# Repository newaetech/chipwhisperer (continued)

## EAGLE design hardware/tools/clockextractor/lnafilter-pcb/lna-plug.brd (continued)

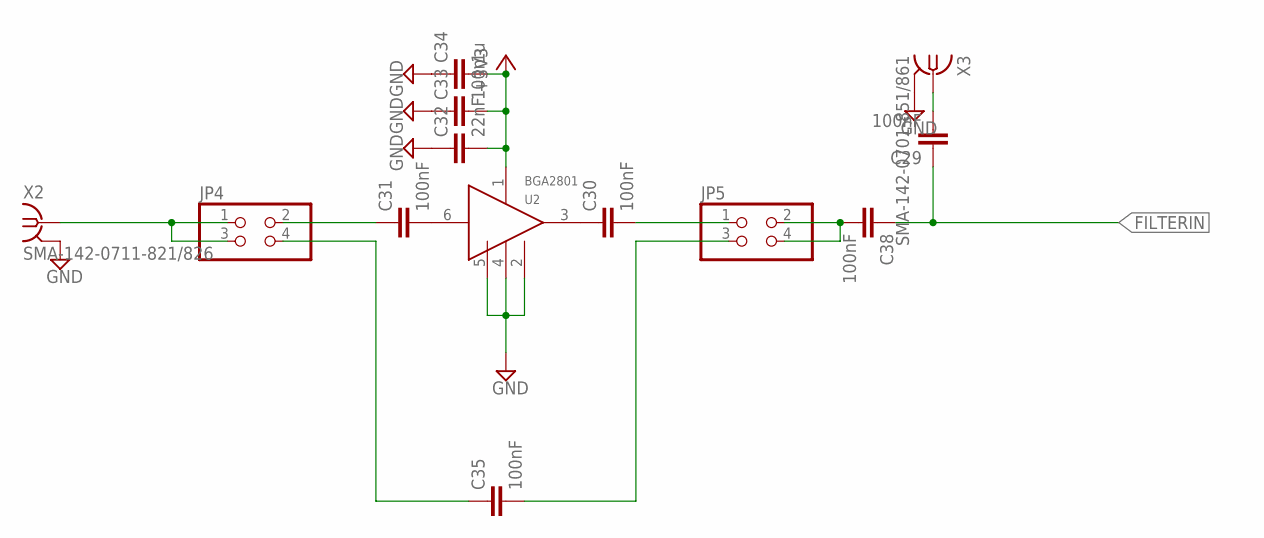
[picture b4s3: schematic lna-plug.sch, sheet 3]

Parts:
C29, C30, C31, C35, C38: 100nF; C0603
C32: 22nF; C0603
C33: 100n; C0603
C34: 1u; C0603
JP4, JP5: PINHD-2X2; 2X02
U2: BGA2801; SOTT323-6
X2: SMA-142-0711-821/826; J502-ND-142-0711-821/826
X3: SMA-142-0701-851/861; J502-ND-142-0701-851/861

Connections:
+3V3: C32.2, C33.2, C34.2, U2.1 (VCC); also elsewhere on the board
FILTERIN: C29.1, C38.1; also elsewhere on the board
GND: C32.1, C33.1, C34.1, U2.2 (GND), U2.4 (GND), U2.5 (GND), X2.G@1 (2), X2.G@2 (2), X2.G@3 (2), X2.G@4 (2), X3.G@1 (2), X3.G@2 (2), X3.G@3 (2), X3.G@4 (2); also elsewhere on the board
unnamed: C38.2, JP5.2, JP5.4
unnamed: C29.2, X3.1
unnamed: C30.1, U2.3 (OUT)
unnamed: C31.2, U2.6 (IN)
unnamed: JP4.1, JP4.3, X2.1
unnamed: C31.1, JP4.2
unnamed: C30.2, JP5.1
unnamed: C35.1, JP4.4
unnamed: C35.2, JP5.3

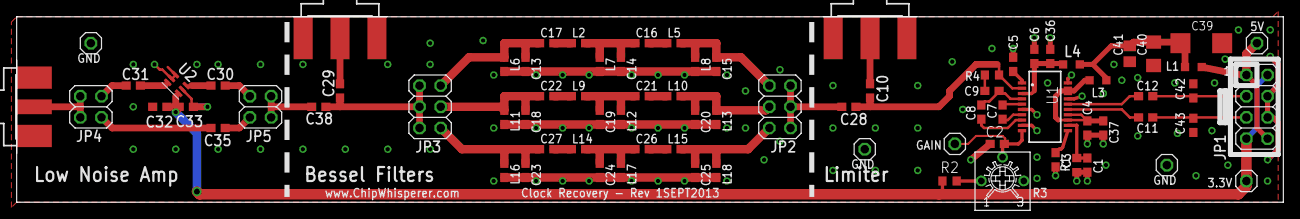
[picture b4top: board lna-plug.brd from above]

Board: 2 copper layers, 151.7 x 22.2 mm, 81 parts (1 on the bottom side), 48 nets.

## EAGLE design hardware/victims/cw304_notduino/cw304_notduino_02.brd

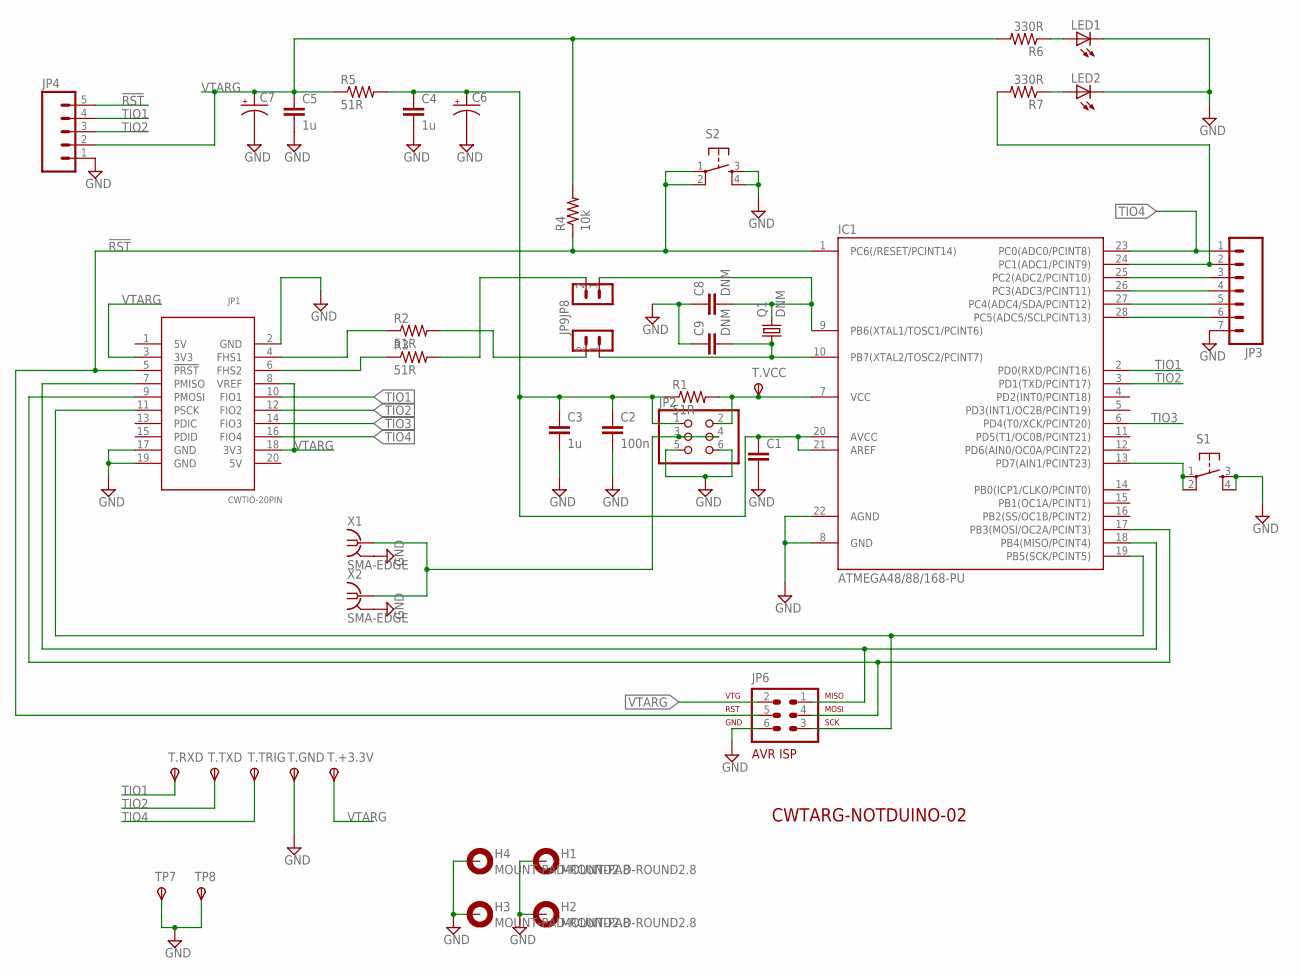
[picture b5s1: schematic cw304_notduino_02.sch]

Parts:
C1: CAPPTH; CAP-PTH-SMALL
C2: 100n; CAP-PTH-SMALL
C3, C4, C5: 1u; CAP-PTH-SMALL
C6, C7: CAP_POLPTH1; CPOL-RADIAL-100UF-25V
C8, C9: DNM; CAP-PTH-SMALL
H1, H2, H3, H4: MOUNT-PAD-ROUND2.8; 2,8-PAD
IC1: ATMEGA48/88/168-PU; DIL28-3
JP1: CWTIO-20PIN; PINSHRD_PTH_2X10
JP2: PINHD-2X3; 2X03
JP3: M07LOCK; 1X07_LOCK
JP4: M05LOCK; 1X05_LOCK
JP6: AVR-ISP-6
JP8, JP9: M02LOCK; 1X02_LOCK
LED1, LED2: LED5MM
Q1: DNM; HC49U-V
R1, R2, R3, R5: 51R; AXIAL-0.4
R4: 10k; AXIAL-0.4
R6, R7: 330R; AXIAL-0.4
S1, S2: TAC_SWITCHPTH; TACTILE-PTH
T.+3.3V, T.GND, T.RXD, T.TRIG, T.TXD: TPSPAD1-13; P1-13
T.VCC: TPSPAD1-17; P1-17
TP7, TP8: TPSPAD1-17; P1-17
X1, X2: SMA-EDGE; J502-ND-142-0711-821/826

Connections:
!RST: IC1.1 (PC6(/RESET/PCINT14)), JP1.5 (!PRST), JP4.5, JP6.5, R4.P$1 (1), S2.1, S2.2
GND: C1.2, C2.2, C3.2, C4.2, C5.2, C6.2 (-), C7.2 (-), C8.1, C9.1, H1.B2,8, H2.B2,8, H3.B2,8, H4.B2,8, IC1.8 (GND), IC1.22 (AGND), JP1.2 (GND), JP1.17 (GND), JP1.19 (GND), JP2.5, JP2.6, JP3.7, JP4.1, JP6.6, LED1.K (C), LED2.K (C), S1.3, S1.4, S2.3, S2.4, T.GND.TP, TP7.TP, TP8.TP, X1.G@1 (2), X1.G@2 (2), X1.G@3 (2), X1.G@4 (2), X2.G@1 (2), X2.G@2 (2), X2.G@3 (2), X2.G@4 (2)
unnamed: LED2.A, R7.P$1 (1)
unnamed: IC1.18 (PB4(MISO/PCINT4)), JP1.7 (PMISO), JP6.1
unnamed: IC1.17 (PB3(MOSI/OC2A/PCINT3)), JP1.9 (PMOSI), JP6.4
unnamed: JP1.4 (FHS1), R2.P$1 (1)
unnamed: JP1.6 (FHS2), R3.P$1 (1)
unnamed: IC1.19 (PB5(SCK/PCINT5)), JP1.11 (PSCK), JP6.3
unnamed: IC1.7 (VCC), JP2.2, R1.P$2 (2), T.VCC.TP
unnamed: LED1.A, R6.P$1 (1)
unnamed: C1.1, C2.1, C3.1, C4.1, C6.1 (+), IC1.20 (AVCC), IC1.21 (AREF), JP2.1, R1.P$1 (1), R5.P$2 (2)
unnamed: C8.2, IC1.9 (PB6(XTAL1/TOSC1/PCINT6)), JP8.1, Q1.2
unnamed: IC1.13 (PD7(AIN1/PCINT23)), S1.1, S1.2
unnamed: IC1.24 (PC1(ADC1/PCINT9)), JP3.2, R7.P$2 (2)
unnamed: IC1.25 (PC2(ADC2/PCINT10)), JP3.3
unnamed: IC1.26 (PC3(ADC3/PCINT11)), JP3.4
unnamed: IC1.27 (PC4(ADC4/SDA/PCINT12)), JP3.5
unnamed: IC1.28 (PC5(ADC5/SCLPCINT13)), JP3.6
unnamed: JP2.3, JP2.4, X1.1, X2.1
unnamed: C9.2, IC1.10 (PB7(XTAL2/TOSC2/PCINT7)), JP9.1, Q1.1
THS1: JP9.2, R2.P$2 (2)
THS2: JP8.2, R3.P$2 (2)
TIO1: IC1.2 (PD0(RXD/PCINT16)), JP1.10 (FIO1), JP4.4, T.RXD.TP
TIO2: IC1.3 (PD1(TXD/PCINT17)), JP1.12 (FIO2), JP4.3, T.TXD.TP
TIO3: IC1.6 (PD4(T0/XCK/PCINT20)), JP1.14 (FIO3)
TIO4: IC1.23 (PC0(ADC0/PCINT8)), JP1.16 (FIO4), JP3.1, T.TRIG.TP
VTARG: C5.1, C7.1 (+), JP1.3 (3V3), JP1.8 (VREF), JP1.18 (3V3), JP4.2, JP6.2, R4.P$2 (2), R5.P$1 (1), R6.P$2 (2), T.+3.3V.TP

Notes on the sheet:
CWTARG-NOTDUINO-02

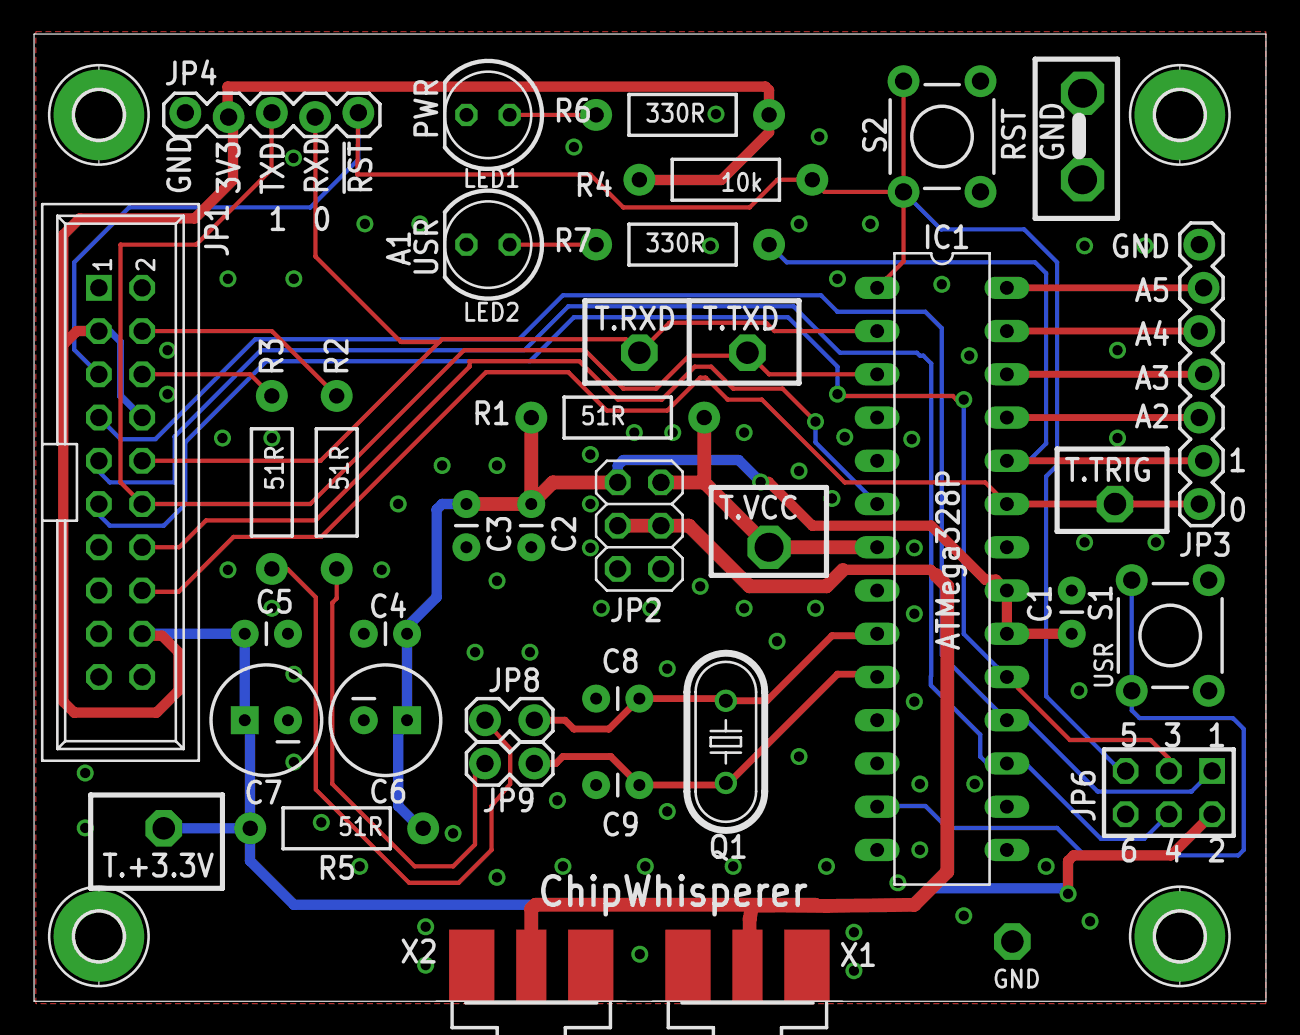
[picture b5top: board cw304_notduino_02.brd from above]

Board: 2 copper layers, 72.4 x 56.8 mm, 43 parts (0 on the bottom side), 27 nets.

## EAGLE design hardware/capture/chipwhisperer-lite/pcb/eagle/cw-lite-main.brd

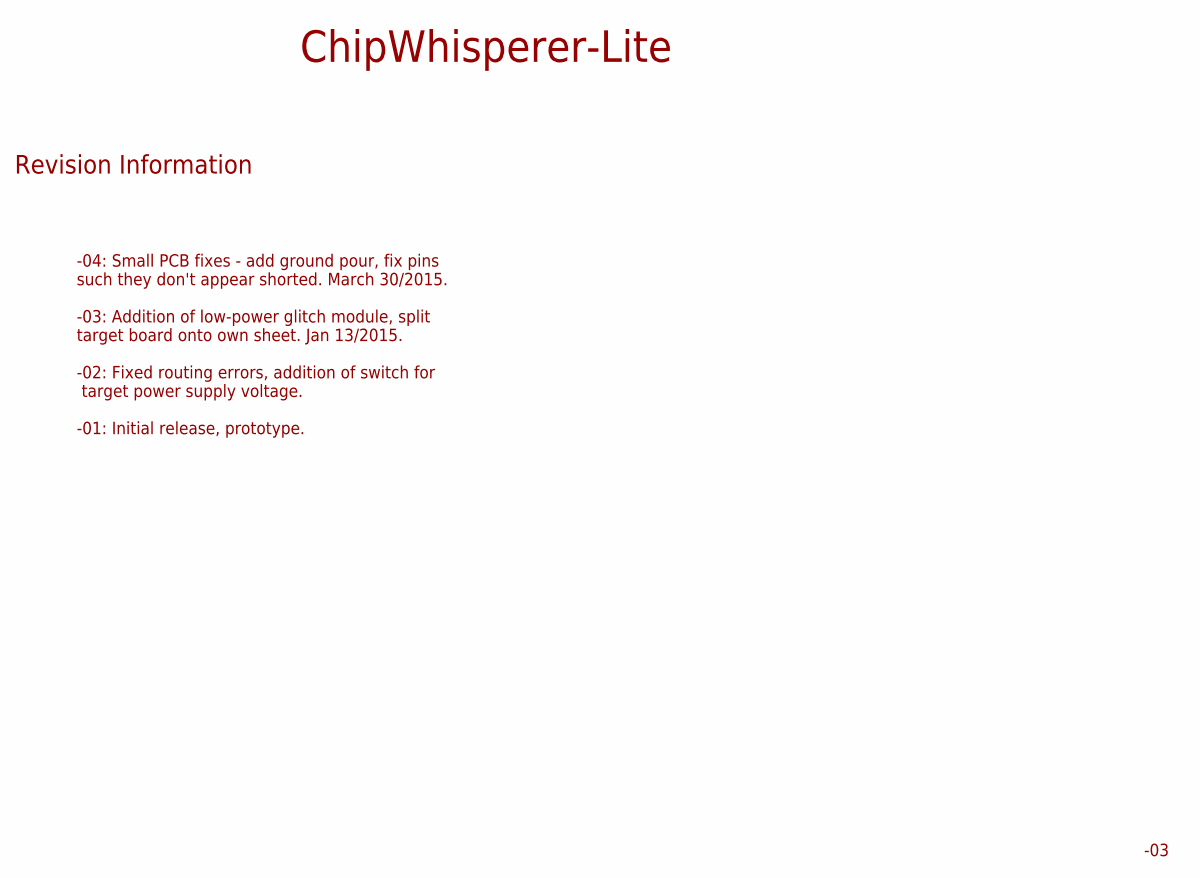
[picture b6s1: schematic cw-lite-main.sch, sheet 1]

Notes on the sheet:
-04: Small PCB fixes - add ground pour, fix pins such they don't appear shorted. March 30/2015. -03: Addition of low-power glitch module, split target board onto own sheet. Jan 13/2015. -02: Fixed routing errors, addition of switch for target power supply voltage. -01: Initial release, prototype.
ChipWhisperer-Lite
Revision Information

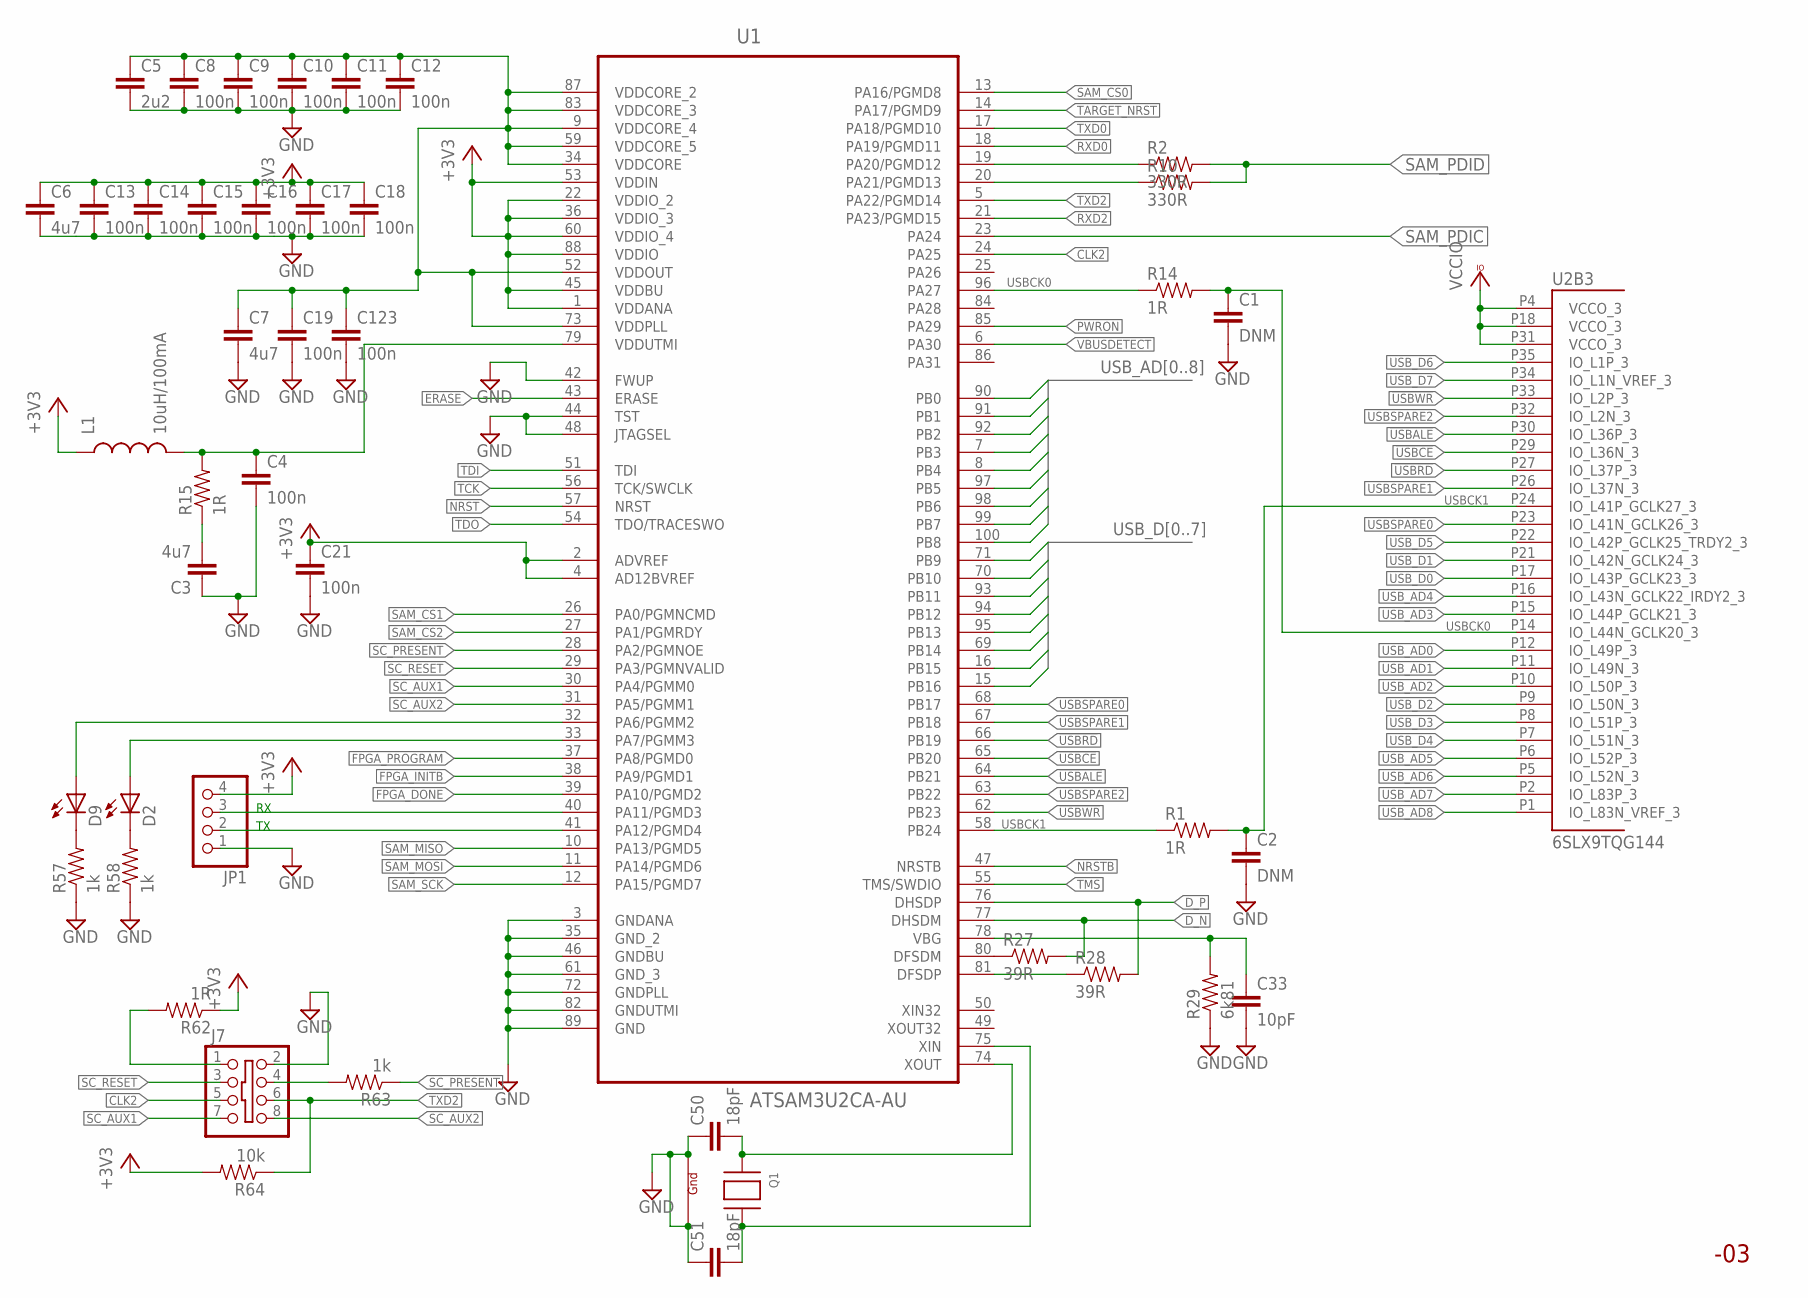
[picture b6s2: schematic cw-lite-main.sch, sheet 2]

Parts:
C1, C2: DNM; 0402C
C3, C6, C7: 4u7; 0603C
C4, C8, C9, C10, C11, C12, C13, C14, C15, C16, C17, C18, C19, C21, C123: 100n; 0402C
C5: 2u2; 0603C
C33: 10pF; 0603C
C50, C51: 18pF; 0402C
D2, D9: LED0603; LED-0603
J7: SHROUD_2X4EDGE; PINSHRD_EDGE_2X04.PAC
JP1: PINHD-1X4; 1X04
L1: 10uH/100mA; 0603
Q1: XTAL-4ABM8G; NX3225; MPN ABM8G-12.000MHZ-4Y-T3
R1, R14: 1R; 0402R
R2, R10: 330R; 0402R
R15, R62: 1R; 0603R
R27, R28: 39R; 0603R
R29: 6k81; 0402R
R57, R58, R63: 1k; 0603R
R64: 10k; 0603R
U1: ATSAM3U2CA-AU; QFP50P1600X1600X160-100N
U2: 6SLX9TQG144; TQ144; MPN XC6SLX9-3TQG144C

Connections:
!USBALE: U1.64 (PB21), U2.P30 (IO_L36P_3)
!USBCE: U1.65 (PB20), U2.P29 (IO_L36N_3)
!USBRD: U1.66 (PB19), U2.P27 (IO_L37P_3)
!USBWR: U1.62 (PB23), U2.P33 (IO_L2P_3)
+3V3: C6.1, C13.1, C14.1, C15.1, C16.1, C17.1, C18.1, C21.1, JP1.4, L1.1, R62.1, R64.2, U1.1 (VDDANA), U1.2 (ADVREF), U1.4 (AD12BVREF), U1.22 (VDDIO_2), U1.36 (VDDIO_3), U1.45 (VDDBU), U1.53 (VDDIN), U1.60 (VDDIO_4), U1.88 (VDDIO); also elsewhere on the board
CLK2: J7.5, U1.24 (PA25); also elsewhere on the board
D_N: R27.2, U1.77 (DHSDM); also elsewhere on the board
D_P: R28.2, U1.76 (DHSDP); also elsewhere on the board
ERASE: U1.43 (ERASE); also elsewhere on the board
FPGA_DONE: U1.39 (PA10/PGMD2); also elsewhere on the board
FPGA_INITB: U1.38 (PA9/PGMD1); also elsewhere on the board
FPGA_PROGRAM: U1.37 (PA8/PGMD0); also elsewhere on the board
GND: C1.2, C2.2, C3.1, C4.2, C5.2, C6.2, C7.2, C8.2, C9.2, C10.2, C11.2, C12.2, C13.2, C14.2, C15.2, C16.2, C17.2, C18.2, C19.2, C21.2, C33.2, C50.1, C51.1, C123.2, J7.2, JP1.1, Q1.2 (G1), Q1.4 (G2), R29.1, R57.1, R58.1, U1.3 (GNDANA), U1.35 (GND_2), U1.42 (FWUP), U1.44 (TST), U1.46 (GNDBU), U1.48 (JTAGSEL), U1.61 (GND_3), U1.72 (GNDPLL), U1.82 (GNDUTMI), U1.89 (GND); also elsewhere on the board
unnamed: R14.1, U1.96 (PA27)
unnamed: JP1.3, U1.40 (PA11/PGMD3)
unnamed: R1.1, U1.58 (PB24)
unnamed: JP1.2, U1.41 (PA12/PGMD4)
unnamed: R2.1, U1.19 (PA20/PGMD12)
unnamed: R10.1, U1.20 (PA21/PGMD13)
unnamed: C3.2, R15.1
unnamed: C4.1, L1.2, R15.2, U1.79 (VDDUTMI)
unnamed: R27.1, U1.80 (DFSDM)
unnamed: C5.1, C7.1, C8.1, C9.1, C10.1, C11.1, C12.1, C19.1, C123.1, U1.9 (VDDCORE_4), U1.34 (VDDCORE), U1.52 (VDDOUT), U1.59 (VDDCORE_5), U1.73 (VDDPLL), U1.83 (VDDCORE_3), U1.87 (VDDCORE_2)
unnamed: R28.1, U1.81 (DFSDP)
unnamed: C33.1, R29.2, U1.78 (VBG)
unnamed: C51.2, Q1.3 (X2), U1.75 (XIN)
unnamed: C50.2, Q1.1 (X1), U1.74 (XOUT)
unnamed: D9.A, U1.32 (PA6/PGMM2)
unnamed: D2.A, U1.33 (PA7/PGMM3)
unnamed: D9.C, R57.2
unnamed: D2.C, R58.2
unnamed: J7.1, R62.2
unnamed: J7.4, R63.2
NRST: U1.57 (NRST); also elsewhere on the board
NRSTB: U1.47 (NRSTB); also elsewhere on the board
PWRON: U1.85 (PA29); also elsewhere on the board
RXD0: U1.18 (PA19/PGMD11); also elsewhere on the board
RXD2: U1.21 (PA23/PGMD15); also elsewhere on the board
SAM_CS0: U1.13 (PA16/PGMD8); also elsewhere on the board
SAM_CS1: U1.26 (PA0/PGMNCMD); also elsewhere on the board
SAM_CS2: U1.27 (PA1/PGMRDY)
SAM_MISO: U1.10 (PA13/PGMD5); also elsewhere on the board
SAM_MOSI: U1.11 (PA14/PGMD6); also elsewhere on the board
SAM_PDIC: U1.23 (PA24); also elsewhere on the board
SAM_PDID: R2.2, R10.2; also elsewhere on the board
SAM_SCK: U1.12 (PA15/PGMD7); also elsewhere on the board
SC_AUX1: J7.7, U1.30 (PA4/PGMM0); also elsewhere on the board
SC_AUX2: J7.8, U1.31 (PA5/PGMM1); also elsewhere on the board
SC_PRESENT: R63.1, U1.28 (PA2/PGMNOE)
SC_RESET: J7.3, U1.29 (PA3/PGMNVALID); also elsewhere on the board
TARGET_NRST: U1.14 (PA17/PGMD9); also elsewhere on the board
TCK: U1.56 (TCK/SWCLK); also elsewhere on the board
TDI: U1.51 (TDI); also elsewhere on the board
TDO: U1.54 (TDO/TRACESWO); also elsewhere on the board
TMS: U1.55 (TMS/SWDIO); also elsewhere on the board
TXD0: U1.17 (PA18/PGMD10); also elsewhere on the board
TXD2: J7.6, R64.1, U1.5 (PA22/PGMD14); also elsewhere on the board
USBCK0: C1.1, R14.2, U2.P14 (IO_L44N_GCLK20_3)
USBCK1: C2.1, R1.2, U2.P24 (IO_L41P_GCLK27_3)
USBSPARE0: U1.68 (PB17), U2.P23 (IO_L41N_GCLK26_3)
USBSPARE1: U1.67 (PB18), U2.P26 (IO_L37N_3)
USBSPARE2: U1.63 (PB22), U2.P32 (IO_L2N_3)
USB_AD0: U1.90 (PB0), U2.P12 (IO_L49P_3)
USB_AD1: U1.91 (PB1), U2.P11 (IO_L49N_3)
USB_AD2: U1.92 (PB2), U2.P10 (IO_L50P_3)
USB_AD3: U1.7 (PB3), U2.P15 (IO_L44P_GCLK21_3)
USB_AD4: U1.8 (PB4), U2.P16 (IO_L43N_GCLK22_IRDY2_3)
USB_AD5: U1.97 (PB5), U2.P6 (IO_L52P_3)
USB_AD6: U1.98 (PB6), U2.P5 (IO_L52N_3)
USB_AD7: U1.99 (PB7), U2.P2 (IO_L83P_3)
USB_AD8: U1.100 (PB8), U2.P1 (IO_L83N_VREF_3)
USB_D0: U1.71 (PB9), U2.P17 (IO_L43P_GCLK23_3)
USB_D1: U1.70 (PB10), U2.P21 (IO_L42N_GCLK24_3)
USB_D2: U1.93 (PB11), U2.P9 (IO_L50N_3)
USB_D3: U1.94 (PB12), U2.P8 (IO_L51P_3)
USB_D4: U1.95 (PB13), U2.P7 (IO_L51N_3)
USB_D5: U1.69 (PB14), U2.P22 (IO_L42P_GCLK25_TRDY2_3)
USB_D6: U1.16 (PB15), U2.P35 (IO_L1P_3)
USB_D7: U1.15 (PB16), U2.P34 (IO_L1N_VREF_3)
VBUSDETECT: U1.6 (PA30); also elsewhere on the board
VCCIO: U2.P4 (VCCO_3), U2.P18 (VCCO_3), U2.P31 (VCCO_3); also elsewhere on the board

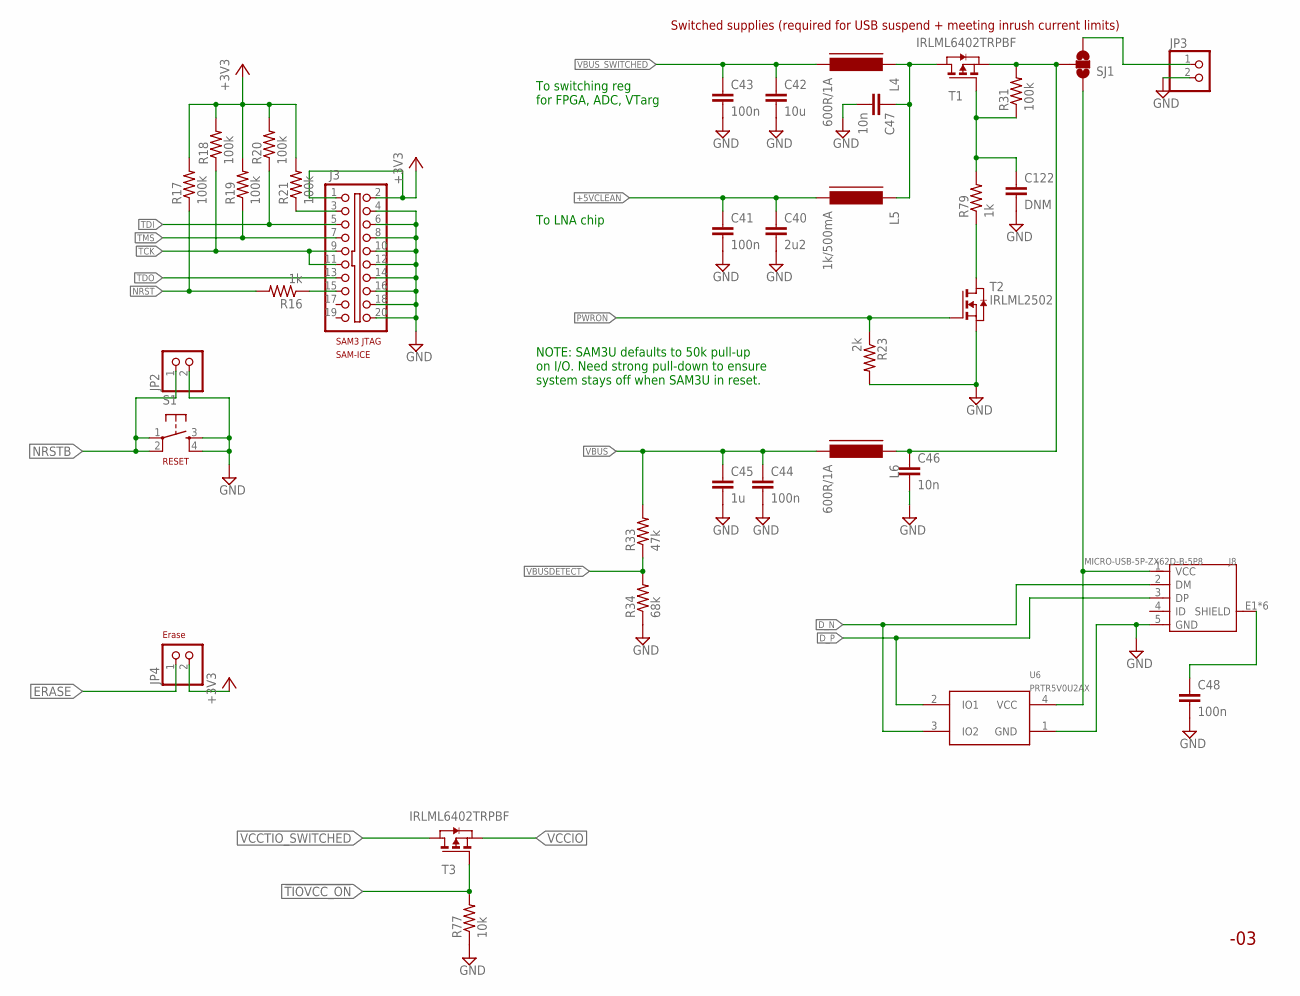
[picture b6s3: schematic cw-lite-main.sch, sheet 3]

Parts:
C40: 2u2; 0603C
C41, C43, C44, C48: 100n; 0603C
C42: 10u; 0603C
C45: 1u; 0603C
C46, C47: 10n; 0603C
C122: DNM; 0603C
J3: SHROUD_2X10-SHROUDED; PINSHRD_PTH_2X10
J8: MICRO-USB-5P-ZX62D-B-5P8; B-SMD-5P-TH; MPN ZX62D-B-5P8
JP2, JP3, JP4: PINHD-1X2; 1X02
L4, L6: 600R/1A; FB603
L5: 1k/500mA; FB603
R16: 1k; 0402R
R17, R18, R19, R20, R21, R31: 100k; 0402R
R23: 2k; 0603R
R33: 47k; 0402R
R34: 68k; 0402R
R77: 10k; 0402R
R79: 1k; 0603R
S1: TAC_SWITCHSMD; TACTILE_SWITCH_SMD
SJ1: SOLDERJUMPER_2WAYPASTE1&2; SJ_3_PASTE1&2
T1, T3: IRLML6402TRPBF; SOT-23; MPN IRLML6402TRPBF
T2: IRLML2502; SOT-23; MPN IRLML2502TRPBF
U6: PRTR5V0U2AX; SOT143B; MPN PRTR5V0U2AX,215

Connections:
!TIOVCC_ON: R77.2, T3.3 (G); also elsewhere on the board
+3V3: J3.1, J3.2, JP4.2, R17.2, R18.2, R19.2, R20.2, R21.2; also elsewhere on the board
+5VCLEAN: C40.1, C41.1, L5.2; also elsewhere on the board
D_N: J8.2 (DM), U6.3 (IO2); also elsewhere on the board
D_P: J8.3 (DP), U6.2 (IO1); also elsewhere on the board
ERASE: JP4.1; also elsewhere on the board
GND: C40.2, C41.2, C42.2, C43.2, C44.2, C45.2, C46.2, C47.2, C48.2, C122.2, J3.4, J3.6, J3.8, J3.10, J3.12, J3.14, J3.16, J3.18, J3.20, J8.5 (GND), JP2.2, JP3.2, R23.2, R34.1, R77.1, S1.3, S1.4, T2.2 (S), U6.1 (GND); also elsewhere on the board
unnamed: J3.3, R21.1
unnamed: J3.15, R16.1
unnamed: JP3.1, SJ1.3
unnamed: C46.1, L6.1, R31.2, SJ1.2, T1.2 (S)
unnamed: J8.1 (VCC), SJ1.1, U6.4 (VCC)
unnamed: C47.1, L4.1, L5.1, T1.1 (D)
unnamed: C122.1, R31.1, R79.2, T1.3 (G)
unnamed: R79.1, T2.1 (D)
unnamed: C48.1, J8.E1 (SHIELD), J8.E2 (SHIELD), J8.P$1 (SHIELD), J8.P$2 (SHIELD), J8.P$3 (SHIELD), J8.P$4 (SHIELD)
NRST: R16.2, R17.1; also elsewhere on the board
NRSTB: JP2.1, S1.1, S1.2; also elsewhere on the board
PWRON: R23.1, T2.3 (G); also elsewhere on the board
TCK: J3.9, J3.11, R18.1; also elsewhere on the board
TDI: J3.5, R20.1; also elsewhere on the board
TDO: J3.13; also elsewhere on the board
TMS: J3.7, R19.1; also elsewhere on the board
VBUS: C44.1, C45.1, L6.2, R33.2; also elsewhere on the board
VBUSDETECT: R33.1, R34.2; also elsewhere on the board
VBUS_SWITCHED: C42.1, C43.1, L4.2; also elsewhere on the board
VCCIO: T3.2 (S); also elsewhere on the board
VCCTIO_SWITCHED: T3.1 (D); also elsewhere on the board

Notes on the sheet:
SAM3 JTAG
SAM-ICE
RESET
Erase
Switched supplies (required for USB suspend + meeting inrush current limits)
NOTE: SAM3U defaults to 50k pull-up on I/O. Need strong pull-down to ensure system stays off when SAM3U in reset.
To switching reg for FPGA, ADC, VTarg
To LNA chip

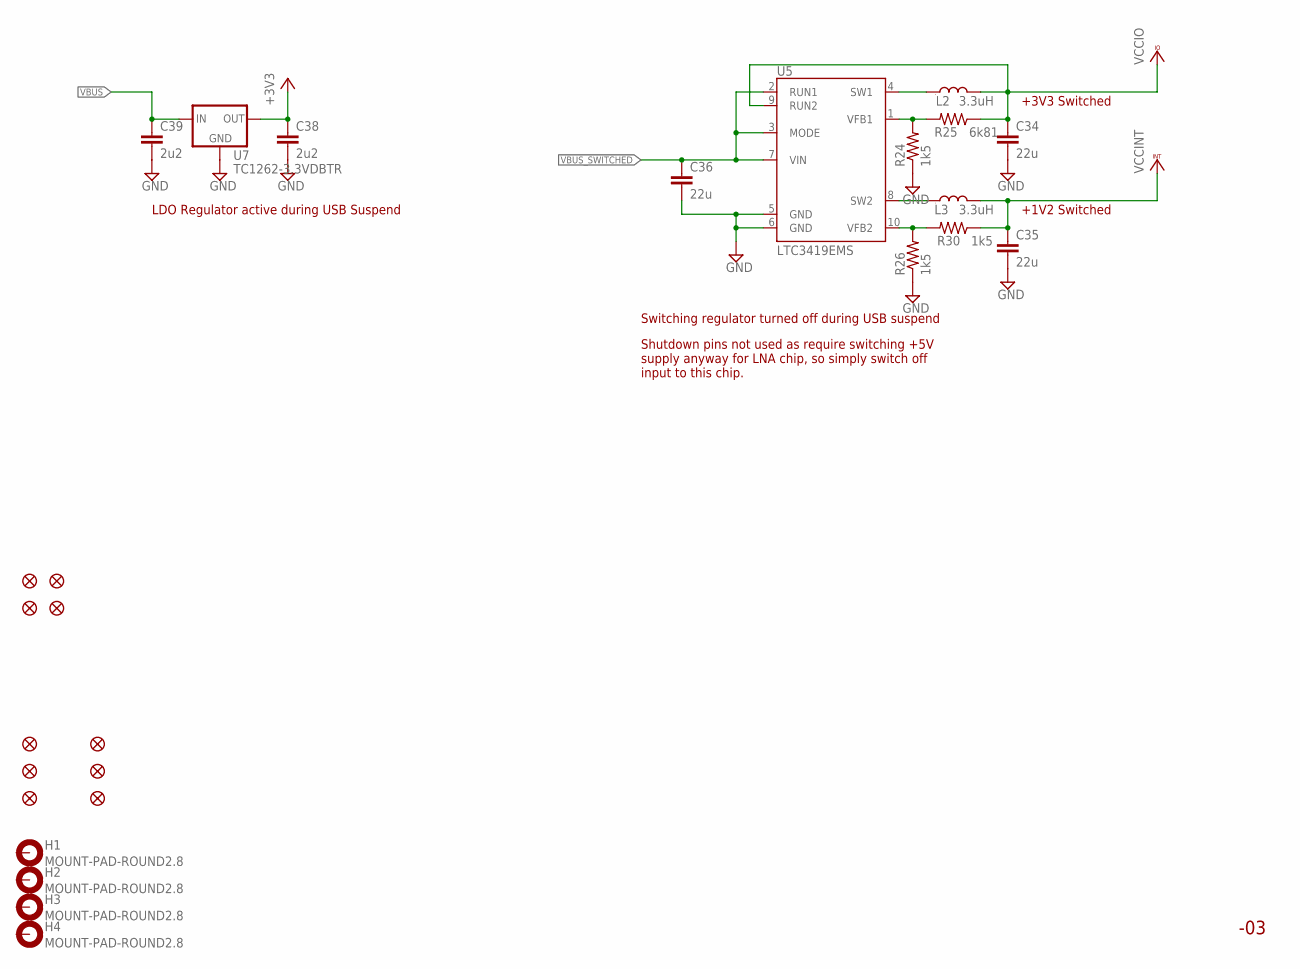
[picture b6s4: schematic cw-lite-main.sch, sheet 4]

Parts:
C34, C35, C36: 22u; 0805
C38, C39: 2u2; 0603C
FID1, FID2, FID3, FID4, FID5, FID6: FIDUCIAL1.5X3; FIDUCIAL-1.5X3
H1, H2, H3, H4: MOUNT-PAD-ROUND2.8; 2,8-PAD
L2: 3.3uH; VLS3015
L3: 3.3uH; VLS3015; MPN VLS3015ET-3R3M
MFID1, MFID2, MFID3, MFID4: FIDUCIALUFIDUCIAL; MICRO-FIDUCIAL
R24, R26, R30: 1k5; 0402R
R25: 6k81; 0402R
U5: LTC3419EMS; MSOP10; MPN LTC3419EMS#PBF
U7: TC1262-3.3VDBTR; SOT223; MPN TC1262-3.3VDBTR

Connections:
+3V3: C38.1, U7.3 (OUT); also elsewhere on the board
FB_1V2: R26.2, R30.2, U5.10 (VFB2)
FB_3V3: R24.2, R25.2, U5.1 (VFB1)
GND: C34.2, C35.2, C36.2, C38.2, C39.2, R24.1, R26.1, U5.5 (GND), U5.6 (GND), U7.2 (GND); also elsewhere on the board
unnamed: L2.1, U5.4 (SW1)
unnamed: L3.1, U5.8 (SW2)
VBUS: C39.1, U7.1 (IN); also elsewhere on the board
VBUS_SWITCHED: C36.1, U5.2 (RUN1), U5.3 (MODE), U5.7 (VIN); also elsewhere on the board
VCCINT: C35.1, L3.2, R30.1; also elsewhere on the board
VCCIO: C34.1, L2.2, R25.1, U5.9 (RUN2); also elsewhere on the board

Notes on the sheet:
+3V3 Switched
+1V2 Switched
LDO Regulator active during USB Suspend
Switching regulator turned off during USB suspend
Shutdown pins not used as require switching +5V supply anyway for LNA chip, so simply switch off input to this chip.

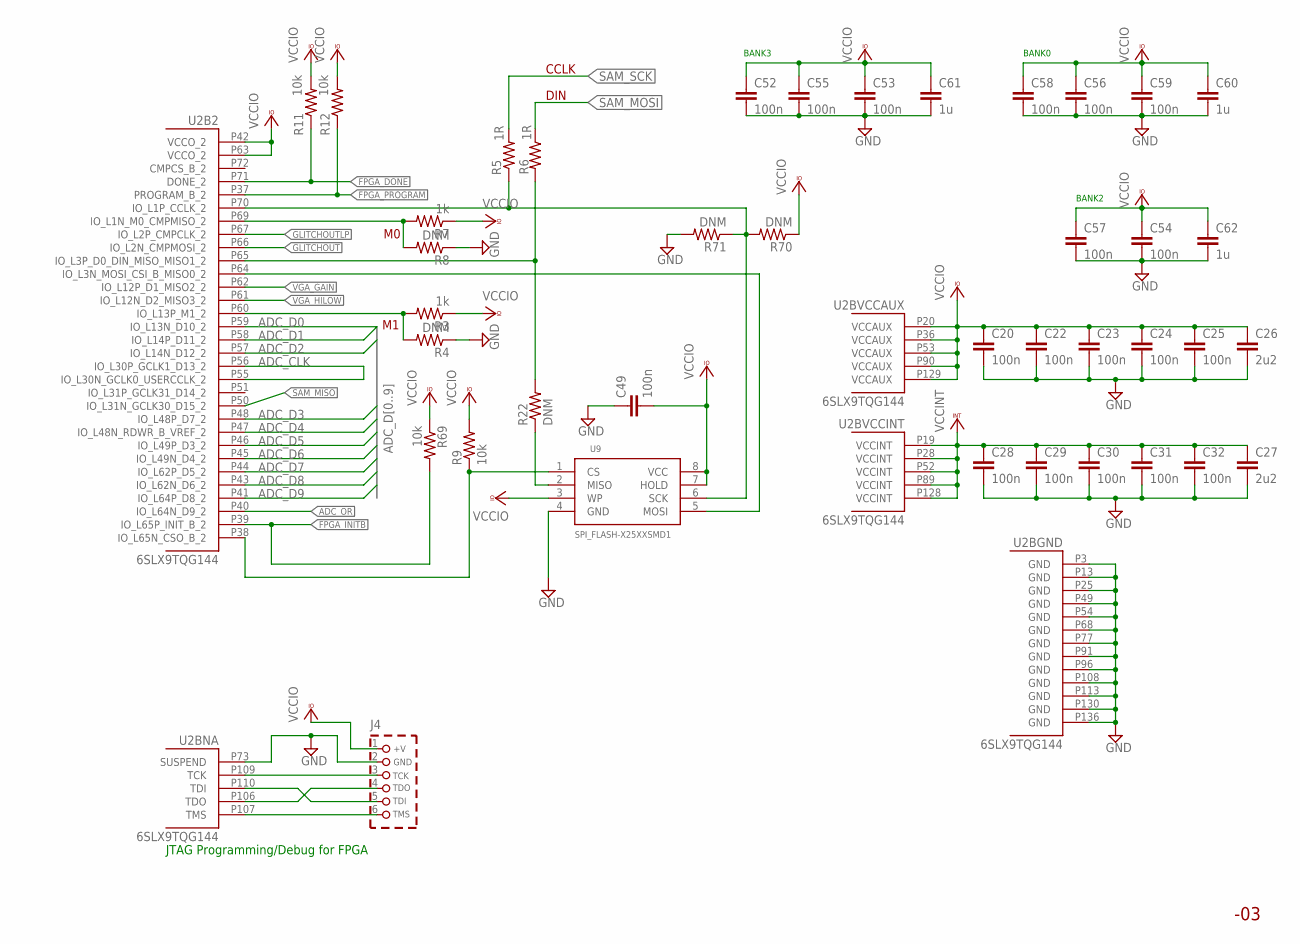
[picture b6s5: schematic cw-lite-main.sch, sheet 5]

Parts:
C20, C22, C23, C24, C25, C28, C29, C30, C31, C32, C52, C53, C54, C55, C56, C57, C58, C59: 100n; 0402C
C26, C27: 2u2; 0603C
C49: 100n; 0603C
C60, C61, C62: 1u; 0603C
J4: CON_HEADER_PRG_XILINX_JTAG6; HEADER_PRG_1X06
R3, R7: 1k; 0603R
R4, R8, R22: DNM; 0603R
R5, R6: 1R; 0402R
R9, R11, R12, R69: 10k; 0402R
R70, R71: DNM; 0402R
U2: 6SLX9TQG144; TQ144; MPN XC6SLX9-3TQG144C
U9: SPI_FLASH-X25XXSMD1; SO08-EIAJ

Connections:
ADC_CLK: U2.P55 (IO_L30N_GCLK0_USERCCLK_2), U2.P56 (IO_L30P_GCLK1_D13_2); also elsewhere on the board
ADC_D0: U2.P59 (IO_L13N_D10_2); also elsewhere on the board
ADC_D1: U2.P58 (IO_L14P_D11_2); also elsewhere on the board
ADC_D2: U2.P57 (IO_L14N_D12_2); also elsewhere on the board
ADC_D3: U2.P48 (IO_L48P_D7_2); also elsewhere on the board
ADC_D4: U2.P47 (IO_L48N_RDWR_B_VREF_2); also elsewhere on the board
ADC_D5: U2.P46 (IO_L49P_D3_2); also elsewhere on the board
ADC_D6: U2.P45 (IO_L49N_D4_2); also elsewhere on the board
ADC_D7: U2.P44 (IO_L62P_D5_2); also elsewhere on the board
ADC_D8: U2.P43 (IO_L62N_D6_2); also elsewhere on the board
ADC_D9: U2.P41 (IO_L64P_D8_2); also elsewhere on the board
ADC_OR: U2.P40 (IO_L64N_D9_2); also elsewhere on the board
FPGA_DONE: R11.1, U2.P71 (DONE_2); also elsewhere on the board
FPGA_INITB: R69.2, U2.P39 (IO_L65P_INIT_B_2); also elsewhere on the board
FPGA_PROGRAM: R12.1, U2.P37 (PROGRAM_B_2); also elsewhere on the board
GLITCHOUT: U2.P66 (IO_L2N_CMPMOSI_2); also elsewhere on the board
GLITCHOUTLP: U2.P67 (IO_L2P_CMPCLK_2); also elsewhere on the board
GND: C20.2, C22.2, C23.2, C24.2, C25.2, C26.2, C27.2, C28.2, C29.2, C30.2, C31.2, C32.2, C49.1, C52.2, C53.2, C54.2, C55.2, C56.2, C57.2, C58.2, C59.2, C60.2, C61.2, C62.2, J4.2 (GND), R4.1, R8.1, R71.2, U2.P3 (GND), U2.P13 (GND), U2.P25 (GND), U2.P49 (GND), U2.P54 (GND), U2.P68 (GND), U2.P73 (SUSPEND), U2.P77 (GND), U2.P91 (GND), U2.P96 (GND), U2.P108 (GND), U2.P113 (GND), U2.P130 (GND), U2.P136 (GND), U9.4 (GND); also elsewhere on the board
unnamed: R5.1, R70.2, R71.1, U2.P70 (IO_L1P_CCLK_2), U9.6 (SCK)
unnamed: R9.1, U2.P38 (IO_L65N_CSO_B_2), U9.1 (CS)
unnamed: R3.2, R4.2, U2.P60 (IO_L13P_M1_2)
unnamed: R7.2, R8.2, U2.P69 (IO_L1N_M0_CMPMISO_2)
unnamed: U2.P64 (IO_L3N_MOSI_CSI_B_MISO0_2), U9.5 (MOSI)
unnamed: R6.2, R22.2, U2.P65 (IO_L3P_D0_DIN_MISO_MISO1_2)
unnamed: R22.1, U9.2 (MISO)
unnamed: J4.6 (TMS), U2.P107 (TMS)
unnamed: J4.5 (TDI), U2.P110 (TDI)
unnamed: J4.4 (TDO), U2.P106 (TDO)
unnamed: J4.3 (TCK), U2.P109 (TCK)
SAM_MISO: U2.P50 (IO_L31N_GCLK30_D15_2); also elsewhere on the board
SAM_MOSI: R6.1; also elsewhere on the board
SAM_SCK: R5.2; also elsewhere on the board
VCCINT: C27.1, C28.1, C29.1, C30.1, C31.1, C32.1, U2.P19 (VCCINT), U2.P28 (VCCINT), U2.P52 (VCCINT), U2.P89 (VCCINT), U2.P128 (VCCINT); also elsewhere on the board
VCCIO: C20.1, C22.1, C23.1, C24.1, C25.1, C26.1, C49.2, C52.1, C53.1, C54.1, C55.1, C56.1, C57.1, C58.1, C59.1, C60.1, C61.1, C62.1, J4.1 (+V), R3.1, R7.1, R9.2, R11.2, R12.2, R69.1, R70.1, U2.P20 (VCCAUX), U2.P36 (VCCAUX), U2.P42 (VCCO_2), U2.P53 (VCCAUX), U2.P63 (VCCO_2), U2.P90 (VCCAUX), U2.P129 (VCCAUX), U9.3 (WP), U9.7 (HOLD), U9.8 (VCC); also elsewhere on the board
VGA_GAIN: U2.P62 (IO_L12P_D1_MISO2_2); also elsewhere on the board
VGA_HILOW: U2.P61 (IO_L12N_D2_MISO3_2); also elsewhere on the board

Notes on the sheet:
BANK2
BANK3
BANK0
CCLK
DIN
JTAG Programming/Debug for FPGA
